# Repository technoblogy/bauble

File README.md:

# Bauble
A globe-shaped festive decoration with 16 coloured LEDs that you can program to flash in different patterns.

For more information see <http://www.technoblogy.com/show?4O86>.

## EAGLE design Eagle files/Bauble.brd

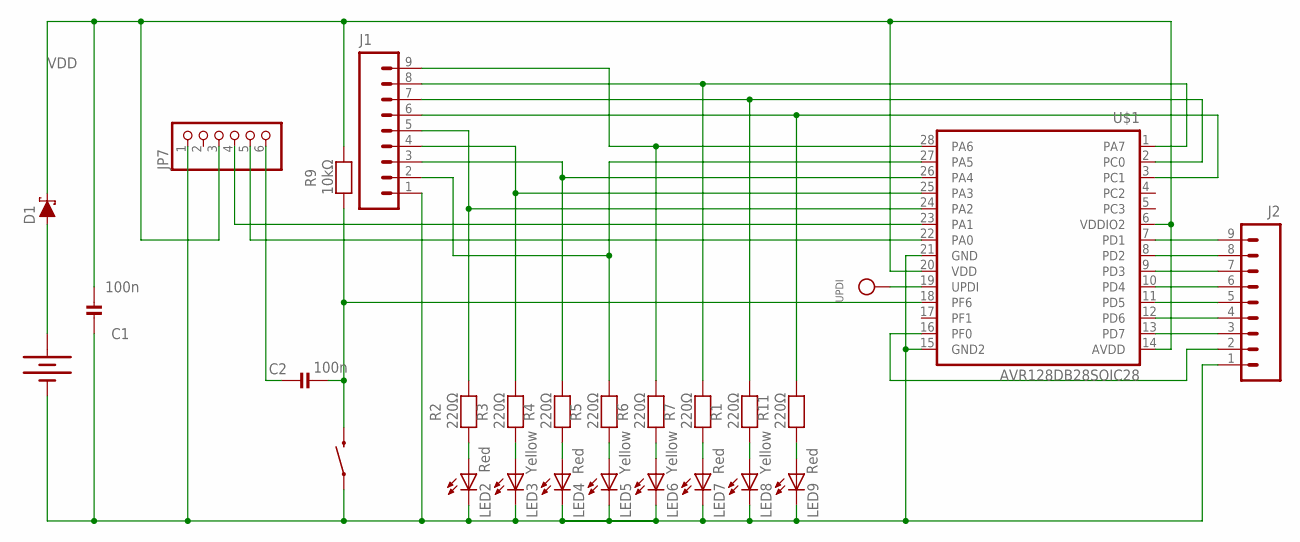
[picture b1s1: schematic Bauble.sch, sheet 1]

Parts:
BAT2: 20mm coincell; BATTCON_20MM_4LEGS
C1, C2: 100n; _0805MP
D1: 3A/10V/280mV; SOD-323
J1, J2: M82MM; 1X10-2MM
JP7: HEADER-1X6ROUND; 1X06_ROUND
LED2, LED4, LED7, LED9: Red; CHIPLED_0805
LED3, LED5, LED6, LED8: Yellow; CHIPLED_0805
R1, R2, R3, R4, R5, R6, R7, R11: 220Ω; _0805MP
R9: 10kΩ; _0805MP
S2: SWITCH-MOMENTARY-2SMD; TACTILE-SWITCH-SMD
U$1: AVR128DB28SOIC28; SO-28W
UPDI: TESTPOINTROUND1MM; TESTPOINT_ROUND_1MM

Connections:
GND: BAT2.NEGATIVE (-), C1.2, J1.1, J2.1, JP7.1, LED2.C, LED3.C, LED4.C, LED5.C, LED6.C, LED7.C, LED8.C, LED9.C, S2.1, U$1.15 (GND2), U$1.21 (GND)
unnamed: J2.2, U$1.16 (PF0)
unnamed: LED2.A, R2.1
unnamed: J1.8, R7.2, U$1.1 (PA7)
unnamed: LED3.A, R3.1
unnamed: J1.7, R1.2, U$1.2 (PC0)
unnamed: J1.5, R2.2, U$1.24 (PA2)
unnamed: C2.1, JP7.6
unnamed: LED4.A, R4.1
unnamed: BAT2.POSITIVE@1 (+), BAT2.POSITIVE@2 (+), BAT2.POSITIVE@3 (+), BAT2.POSITIVE@4 (+), D1.A
unnamed: LED5.A, R5.1
unnamed: LED6.A, R6.1
unnamed: LED7.A, R7.1
unnamed: J1.9, R6.2, U$1.28 (PA6)
unnamed: J1.3, R4.2, U$1.26 (PA4)
unnamed: J1.2, R5.2, U$1.27 (PA5)
unnamed: J1.4, R3.2, U$1.25 (PA3)
unnamed: J2.9, U$1.7 (PD1)
unnamed: U$1.19 (UPDI), UPDI.P$1
unnamed: J1.6, R11.2, U$1.3 (PC1)
unnamed: J2.8, U$1.8 (PD2)
unnamed: J2.7, U$1.9 (PD3)
unnamed: LED9.A, R11.1
unnamed: J2.6, U$1.10 (PD4)
unnamed: LED8.A, R1.1
unnamed: J2.5, U$1.11 (PD5)
unnamed: J2.4, U$1.12 (PD6)
unnamed: J2.3, U$1.13 (PD7)
RESET: C2.2, R9.1, S2.3 (2), U$1.18 (PF6)
RX: JP7.4, U$1.23 (PA1)
TX: JP7.5, U$1.22 (PA0)
VDD: C1.1, D1.C, JP7.3, R9.2, U$1.6 (VDDIO2), U$1.14 (AVDD), U$1.20 (VDD)

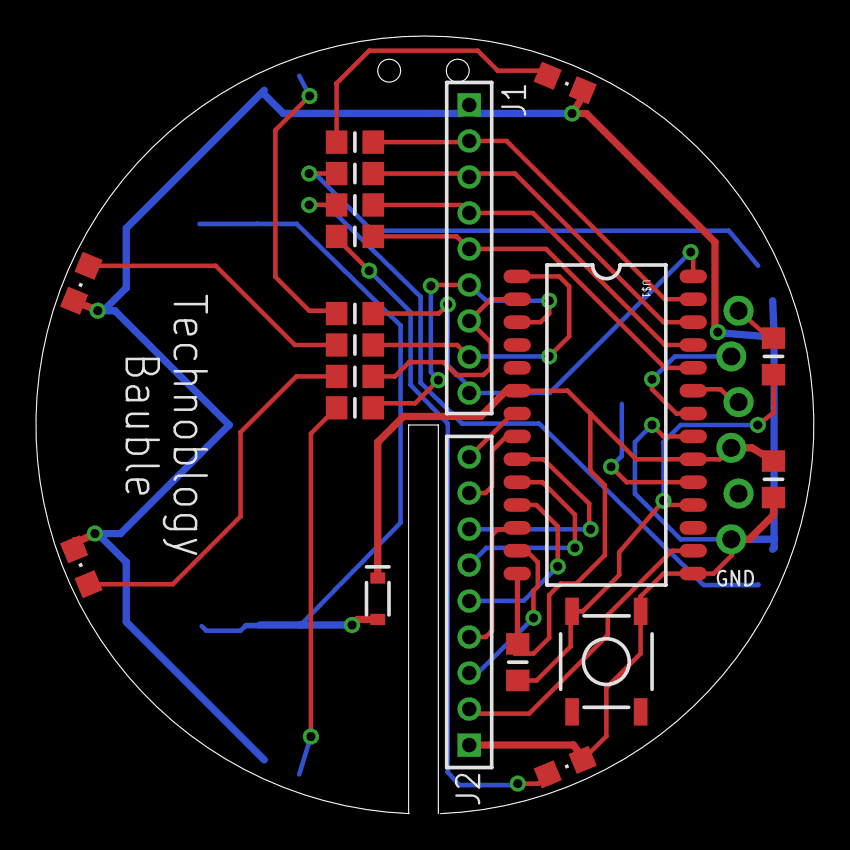
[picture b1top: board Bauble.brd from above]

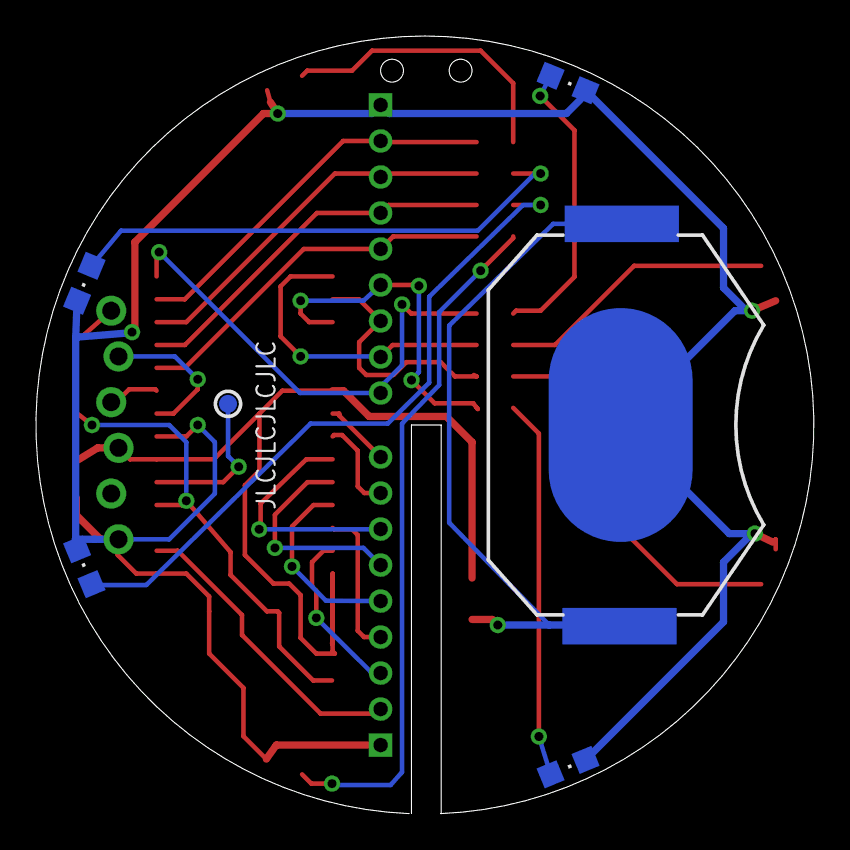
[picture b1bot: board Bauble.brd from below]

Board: 2 copper layers, 43.2 x 43.2 mm, 27 parts (6 on the bottom side), 32 nets.

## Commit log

2025-11-04 Version 1 - 4th November 2025

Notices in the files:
parts and their libraries:
SparkFun-Electromechanical: Licensing: Creative Commons ShareAlike 4.0 International - https://creativecommons.org/licenses/by-sa/4.0
microbuilder: This work is placed in the public domain, and may be freely used for commercial and non-commercial work with the following conditions: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
